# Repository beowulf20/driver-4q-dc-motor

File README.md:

# Projeto Driver 4Q 2020/1

## Especificação
- Acionamento do motor [M 210 1K2 24V](http://motron.com.br/produtos/210/curvas/m210-iverln-1k2-24v.pdf) 

## Abrangência
- Fonte Primária (220Vac)
> Trafo + Retificador + Filtro Capacitivo (ou fonte chaveada)
- Circuito Modulador PWM (escolher CI comercial ou microcontrolador com software)
- Driver
> Ponte comercial ou MOSFET (incluir driver do gate)

# Referências

[Using Spice To Model DC Motors](https://www.precisionmicrodrives.com/content/ab-025-using-spice-to-model-dc-motors/)
[LTSpice Tutorial - Modeling a DC brushed motor](https://www.youtube.com/watch?v=Wc4XzTrWSpo)

[M210 1K2 24V Datasheet](docs/m210-iverln-1k2-24v.pdf)

[Guia Prático Proteção de Motores](docs/protecao_motores.pdf)

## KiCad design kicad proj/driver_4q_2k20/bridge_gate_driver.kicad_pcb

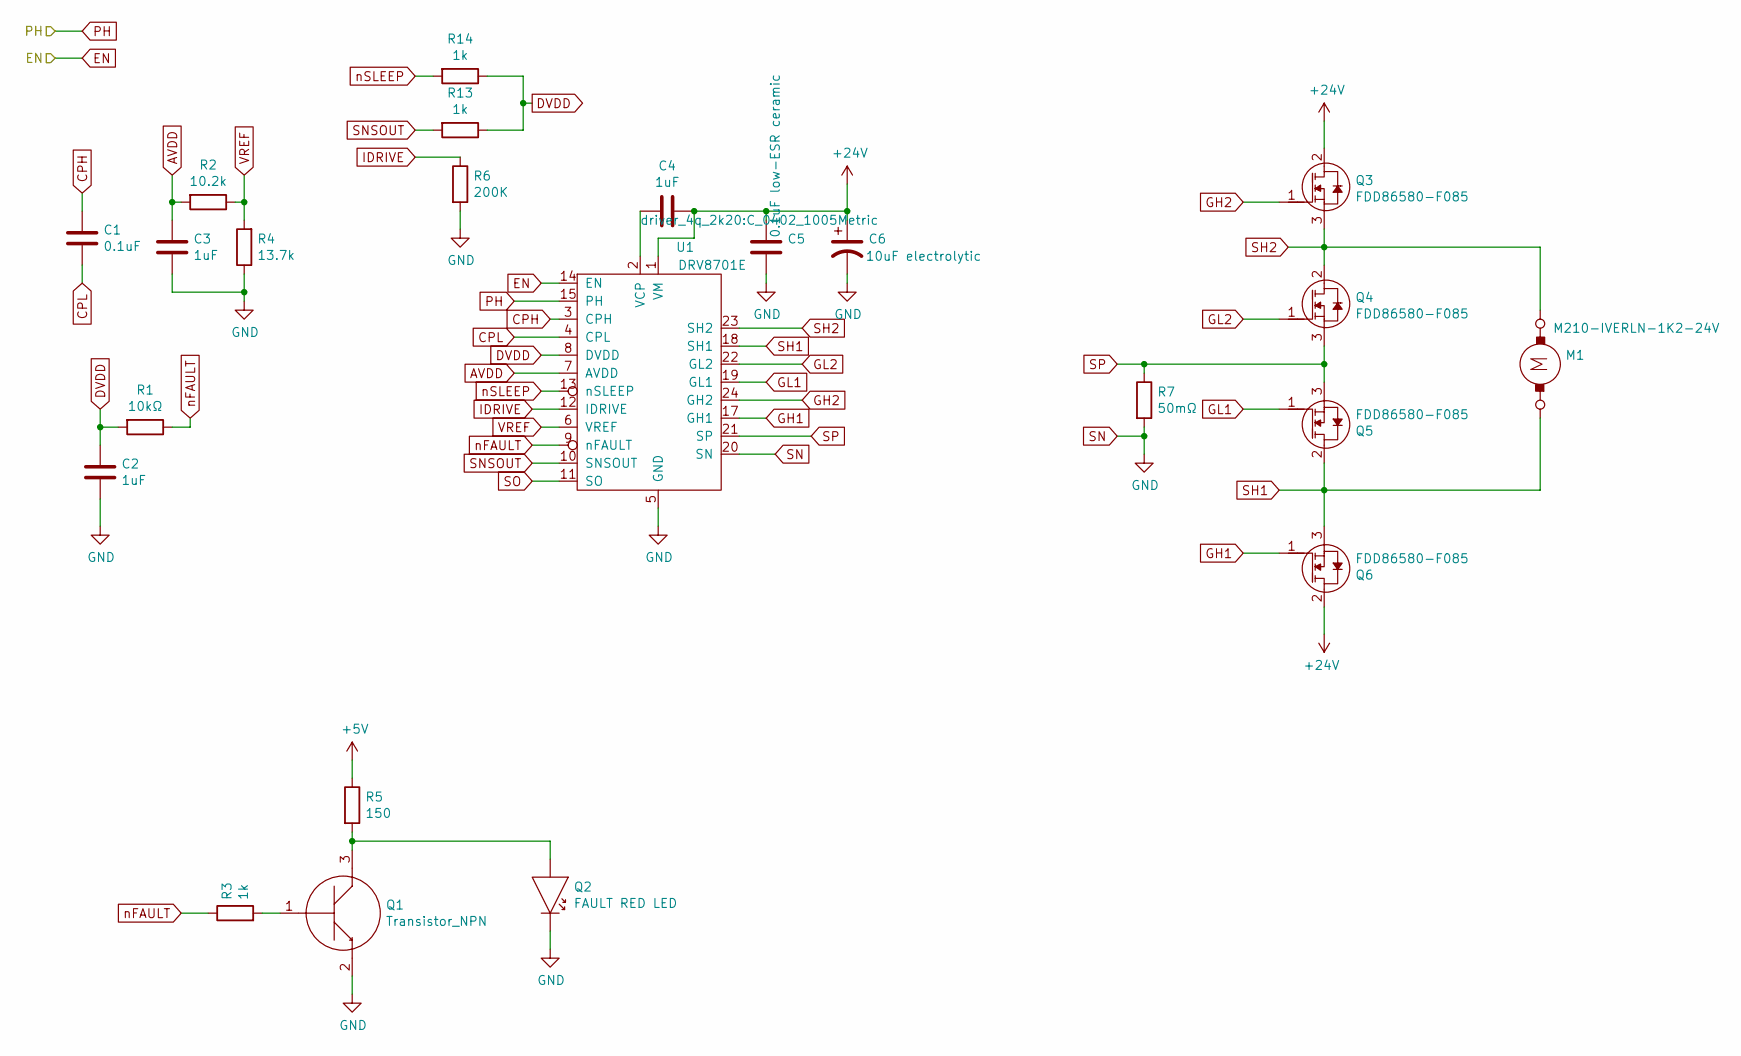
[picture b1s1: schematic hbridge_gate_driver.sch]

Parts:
C1: 0.1uF; C_0402_1005Metric
C2, C3, C4: 1uF; C_0402_1005Metric
C5: 0.1uF low-ESR ceramic; C_0402_1005Metric
C6: 10uF electrolytic; CP_Radial_D5.0mm_P2.00mm
M1: M210-IVERLN-1K2-24V; 395430203
Q1: Transistor_NPN; SOT-23
Q2: FAULT RED LED; LTL-10224W-RED
Q3, Q4, Q5, Q6: FDD86580-F085; TO-252-3_TabPin2
R1: 10kΩ; R_0402_1005Metric
R2: 10.2k; R_0402_1005Metric
R3: 1k; C_0402_1005Metric
R4: 13.7k; R_0402_1005Metric
R5: 150; C_0402_1005Metric
R6: 200K; C_0402_1005Metric
R7: 50mΩ; R_0402_1005Metric
R13, R14: 1k; R_0402_1005Metric
U1: DRV8701E; DRV8701

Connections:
24V: C4.2, C5.2, C6.1, Q3.2 (D), Q6.2 (D), U1.1 (VM); also elsewhere on the board
+5V: R5.1; also elsewhere on the board
AVDD: C3.1, R2.2, U1.7 (AVDD)
CPH: C1.2, U1.3 (CPH)
CPL: C1.1, U1.4 (CPL)
DIR: U1.15 (PH); also elsewhere on the board
DVDD: C2.1, R1.2, R13.1, R14.1, U1.8 (DVDD)
EN: U1.14 (EN); also elsewhere on the board
GH1: Q6.1 (G), U1.17 (GH1)
GH2: Q3.1 (G), U1.24 (GH2)
GL1: Q5.1 (G), U1.19 (GL1)
GL2: Q4.1 (G), U1.22 (GL2)
GND: C2.2, C3.2, C5.1, C6.2, Q1.2, Q2.2, R4.1, R6.2, R7.2, U1.5 (GND), U1.20 (SN); also elsewhere on the board
IDRIVE: R6.1, U1.12 (IDRIVE)
unnamed: C4.1, U1.2 (VCP)
unnamed: Q1.1, R3.2
unnamed: Q1.3, Q2.1 (K), R5.2
SH1: M1.2, Q5.2 (D), Q6.3 (S), U1.18 (SH1)
SH2: M1.1, Q3.3 (S), Q4.2 (D), U1.23 (SH2)
SNSOUT: R13.2, U1.10 (SNSOUT)
SO: U1.11 (SO)
SP: Q4.3 (S), Q5.3 (S), R7.1, U1.21 (SP)
VREF: R2.1, R4.2, U1.6 (VREF)
nFAULT: R1.1, R3.1, U1.9 (nFAULT)
nSLEEP: R14.2, U1.13 (nSLEEP)

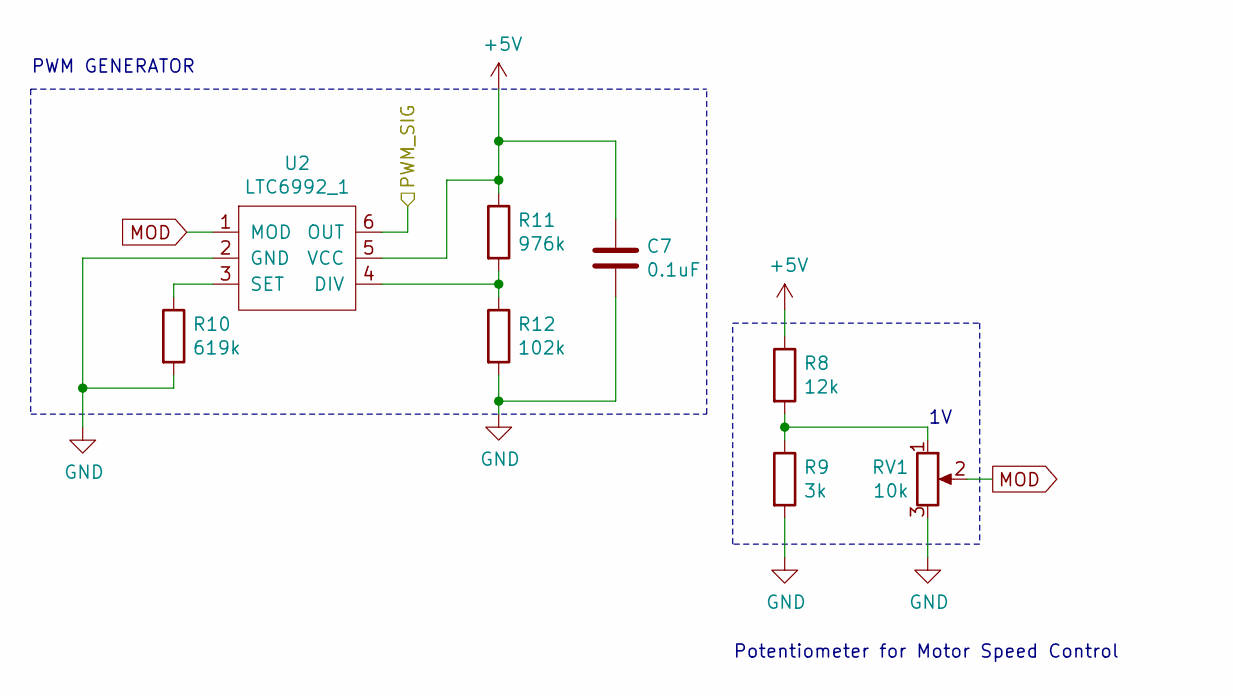
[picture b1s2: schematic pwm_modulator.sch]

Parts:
C7: 0.1uF; C_0402_1005Metric
R8: 12k; R_0402_1005Metric
R9: 3k; R_0402_1005Metric
R10: 619k; R_0402_1005Metric
R11: 976k; R_0402_1005Metric
R12: 102k; R_0402_1005Metric
RV1: 10k; RK09D111
U2: LTC6992_1; TSOT-23-6

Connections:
+5V: C7.1, R8.1, R11.1, U2.5 (VCC); also elsewhere on the board
EN: U2.6 (OUT); also elsewhere on the board
GND: C7.2, R9.2, R10.2, R12.2, RV1.3, U2.2 (GND); also elsewhere on the board
MOD: RV1.2, U2.1 (MOD)
unnamed: R8.2, R9.1, RV1.1
unnamed: R10.1, U2.3 (SET)
unnamed: R11.2, R12.1, U2.4 (DIV)

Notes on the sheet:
Potentiometer for Motor Speed Control
PWM GENERATOR

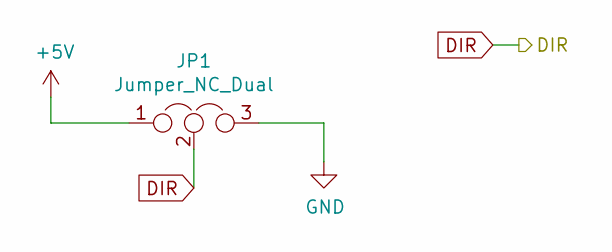
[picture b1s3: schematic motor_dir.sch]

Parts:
JP1: Jumper_NC_Dual; PinHeader_1x03_P1.27mm_Vertical

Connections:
+5V: JP1.1; also elsewhere on the board
DIR: JP1.2; also elsewhere on the board
GND: JP1.3; also elsewhere on the board

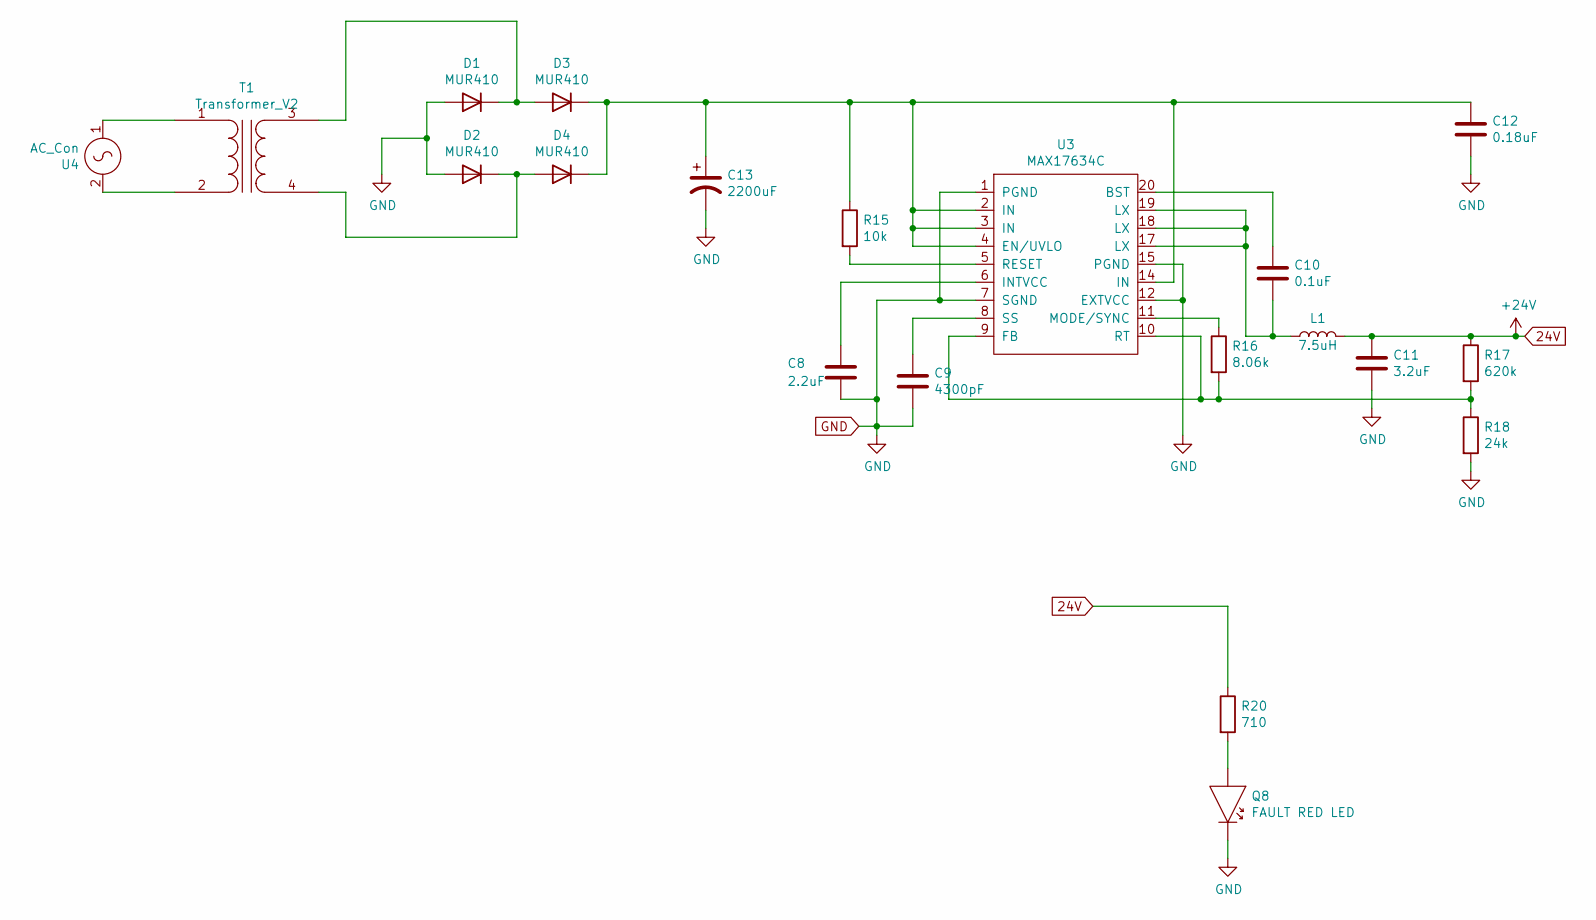
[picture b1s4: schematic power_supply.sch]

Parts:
C8: 2.2uF; C_0402_1005Metric
C9: 4300pF; C_0402_1005Metric
C10: 0.1uF; C_0402_1005Metric
C11: 3.2uF; C_0402_1005Metric
C12: 0.18uF; C_0402_1005Metric
C13: 2200uF; CP_Radial_D5.0mm_P2.00mm
D1, D2, D3, D4: MUR410; D_DO-41_SOD81_P10.16mm_Horizontal
L1: 7.5uH; L_TracoPower_TCK-047_5.2x5.8mm
Q8: FAULT RED LED; LTL-10224W-RED
R15: 10k; R_0402_1005Metric
R16: 8.06k; R_0402_1005Metric
R17: 620k; R_0402_1005Metric
R18: 24k; R_0402_1005Metric
R20: 710; C_0402_1005Metric
T1: Transformer_V2; Transformer_96x87
U3: MAX17634C; TQFN-20-1EP_5x5mm_P0.65mm_EP3.1x3.1mm
U4: AC_Con; 395430203

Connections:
24V: C11.1, L1.2, R17.1, R20.1; also elsewhere on the board
GND: C8.2, C9.2, C11.2, C12.2, C13.2, D1.2 (A), D2.2 (A), Q8.2, R18.2, U3.1 (PGND), U3.7 (SGND), U3.12 (EXTVCC), U3.15 (PGND); also elsewhere on the board
unnamed: C8.1, U3.6 (INTVCC)
unnamed: C9.1, U3.8 (SS)
unnamed: C10.1, U3.20 (BST)
unnamed: C10.2, L1.1, U3.17 (LX), U3.18 (LX), U3.19 (LX)
unnamed: C12.1, C13.1, D3.1 (K), D4.1 (K), R15.1, U3.2 (IN), U3.3 (IN), U3.4 (EN/UVLO), U3.14 (IN)
unnamed: D1.1 (K), D3.2 (A), T1.3 (SB)
unnamed: D2.1 (K), D4.2 (A), T1.4 (SA)
unnamed: Q8.1 (K), R20.2
unnamed: R15.2, U3.5 (RESET)
unnamed: R16.1, U3.11 (MODE/SYNC)
unnamed: R16.2, R17.2, R18.1, U3.9 (FB), U3.10 (RT)
unnamed: T1.1 (AA), U4.1
unnamed: T1.2 (AB), U4.2

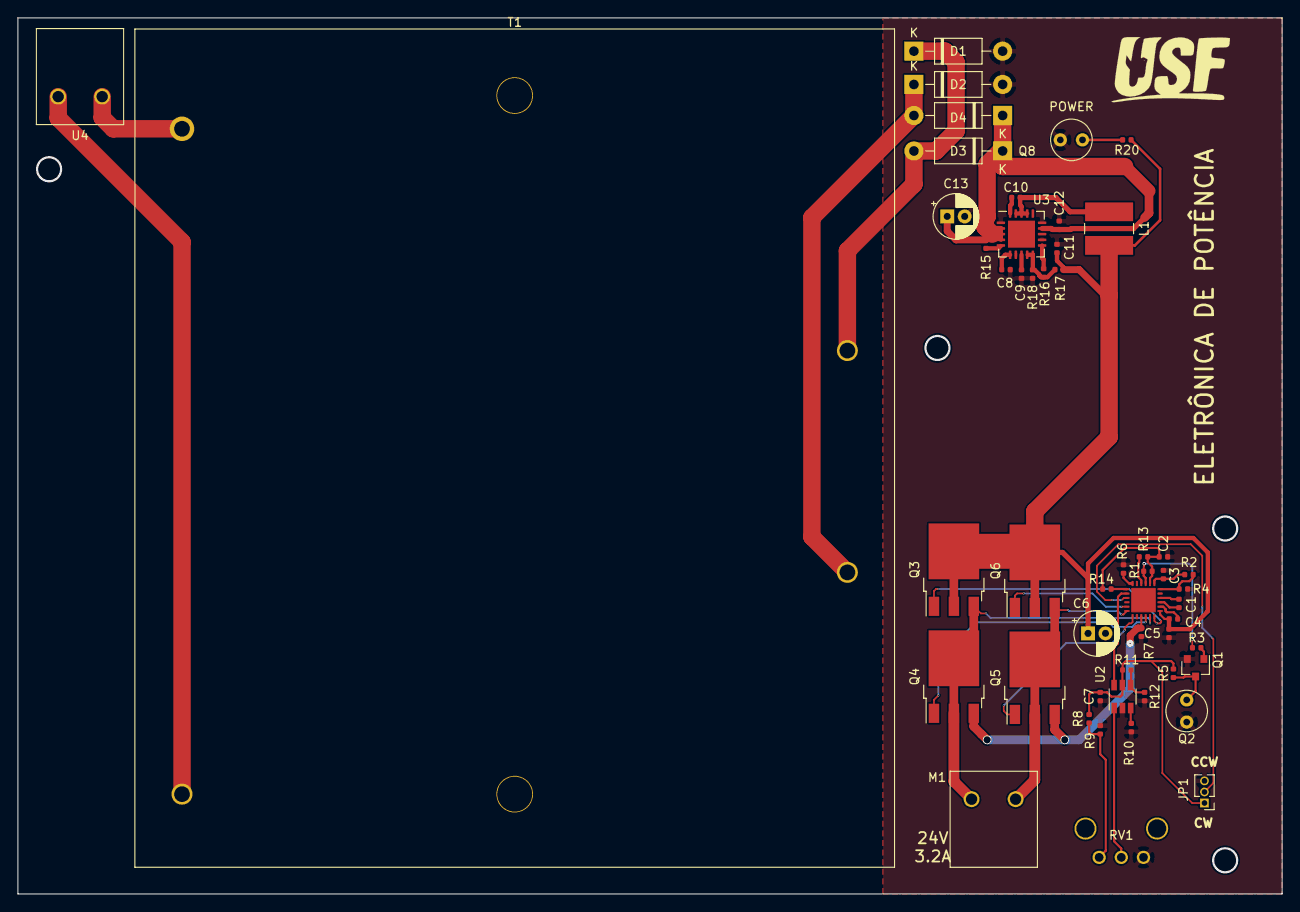
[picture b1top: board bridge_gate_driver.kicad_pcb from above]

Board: 2 copper layers, 144.8 x 100.3 mm, 52 parts (0 on the bottom side), 41 nets.

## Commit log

2020-05-20 Commit Inicial
2020-05-20 Adicionado referencias
2020-06-08 add documentação base
2020-06-08 circuito com gate driver + ponte H + modulador pwm
2020-06-22 adicionado arquivos step, docs e footprints
2020-06-22 added power supply and new transformer
